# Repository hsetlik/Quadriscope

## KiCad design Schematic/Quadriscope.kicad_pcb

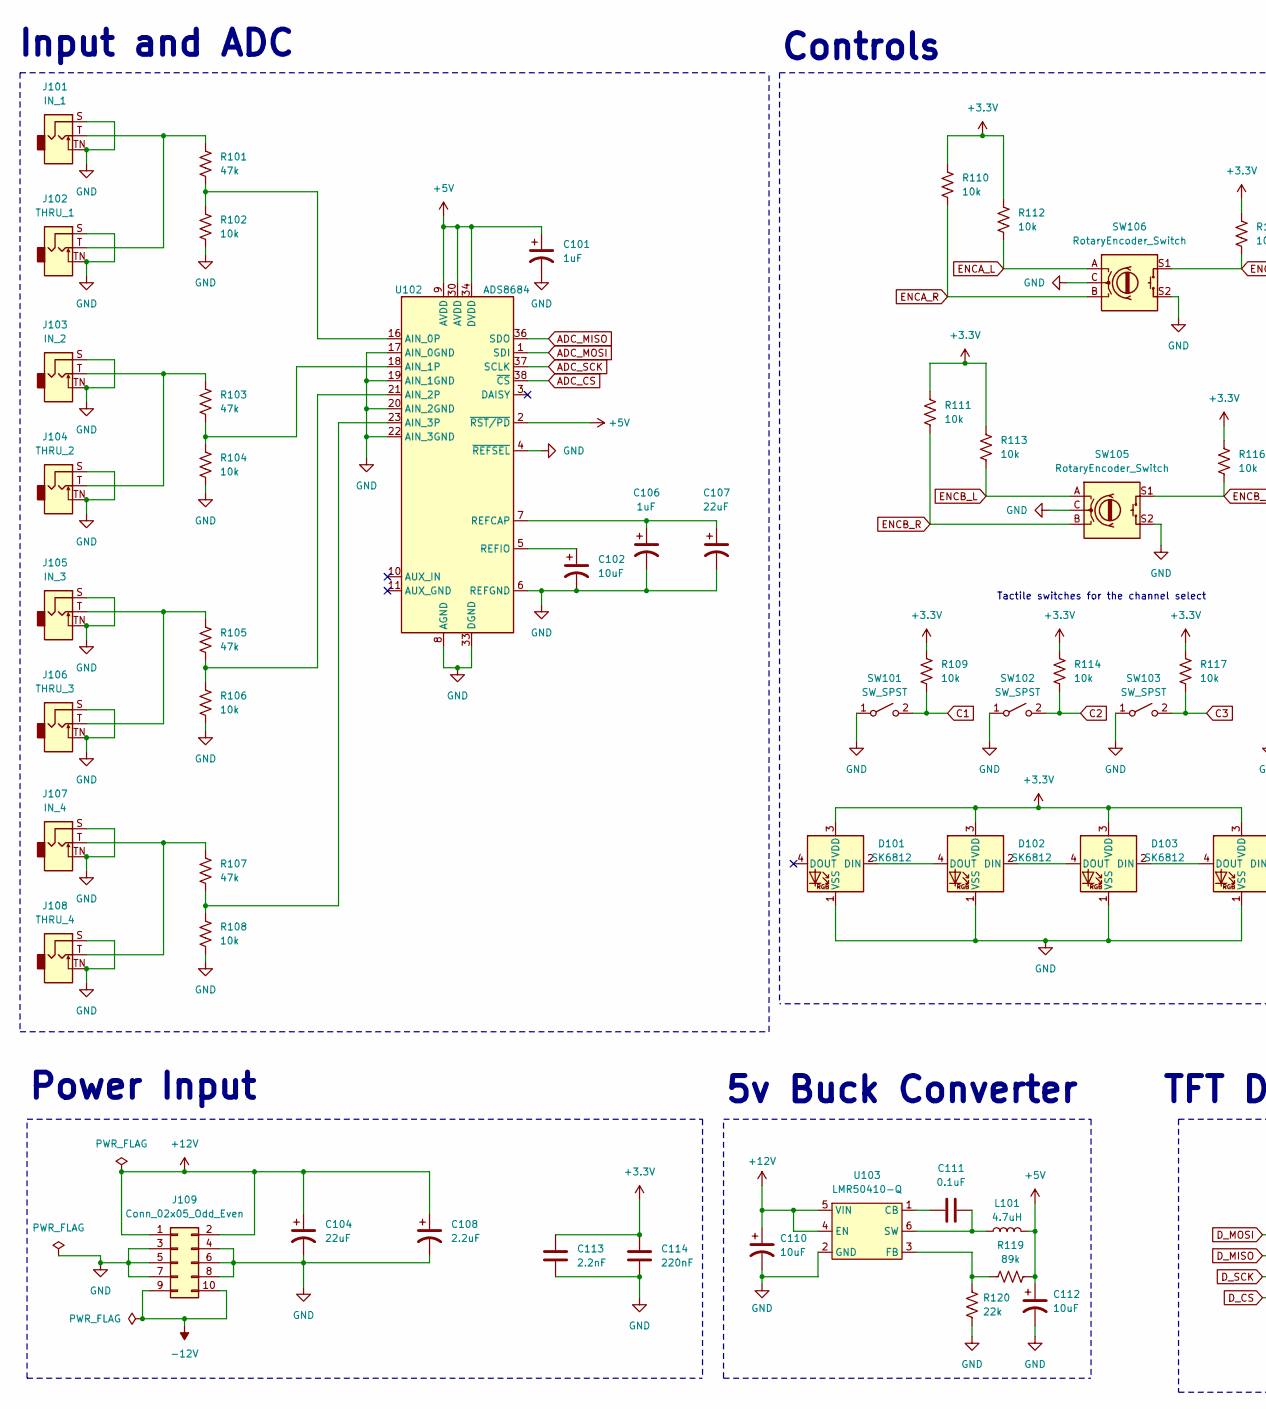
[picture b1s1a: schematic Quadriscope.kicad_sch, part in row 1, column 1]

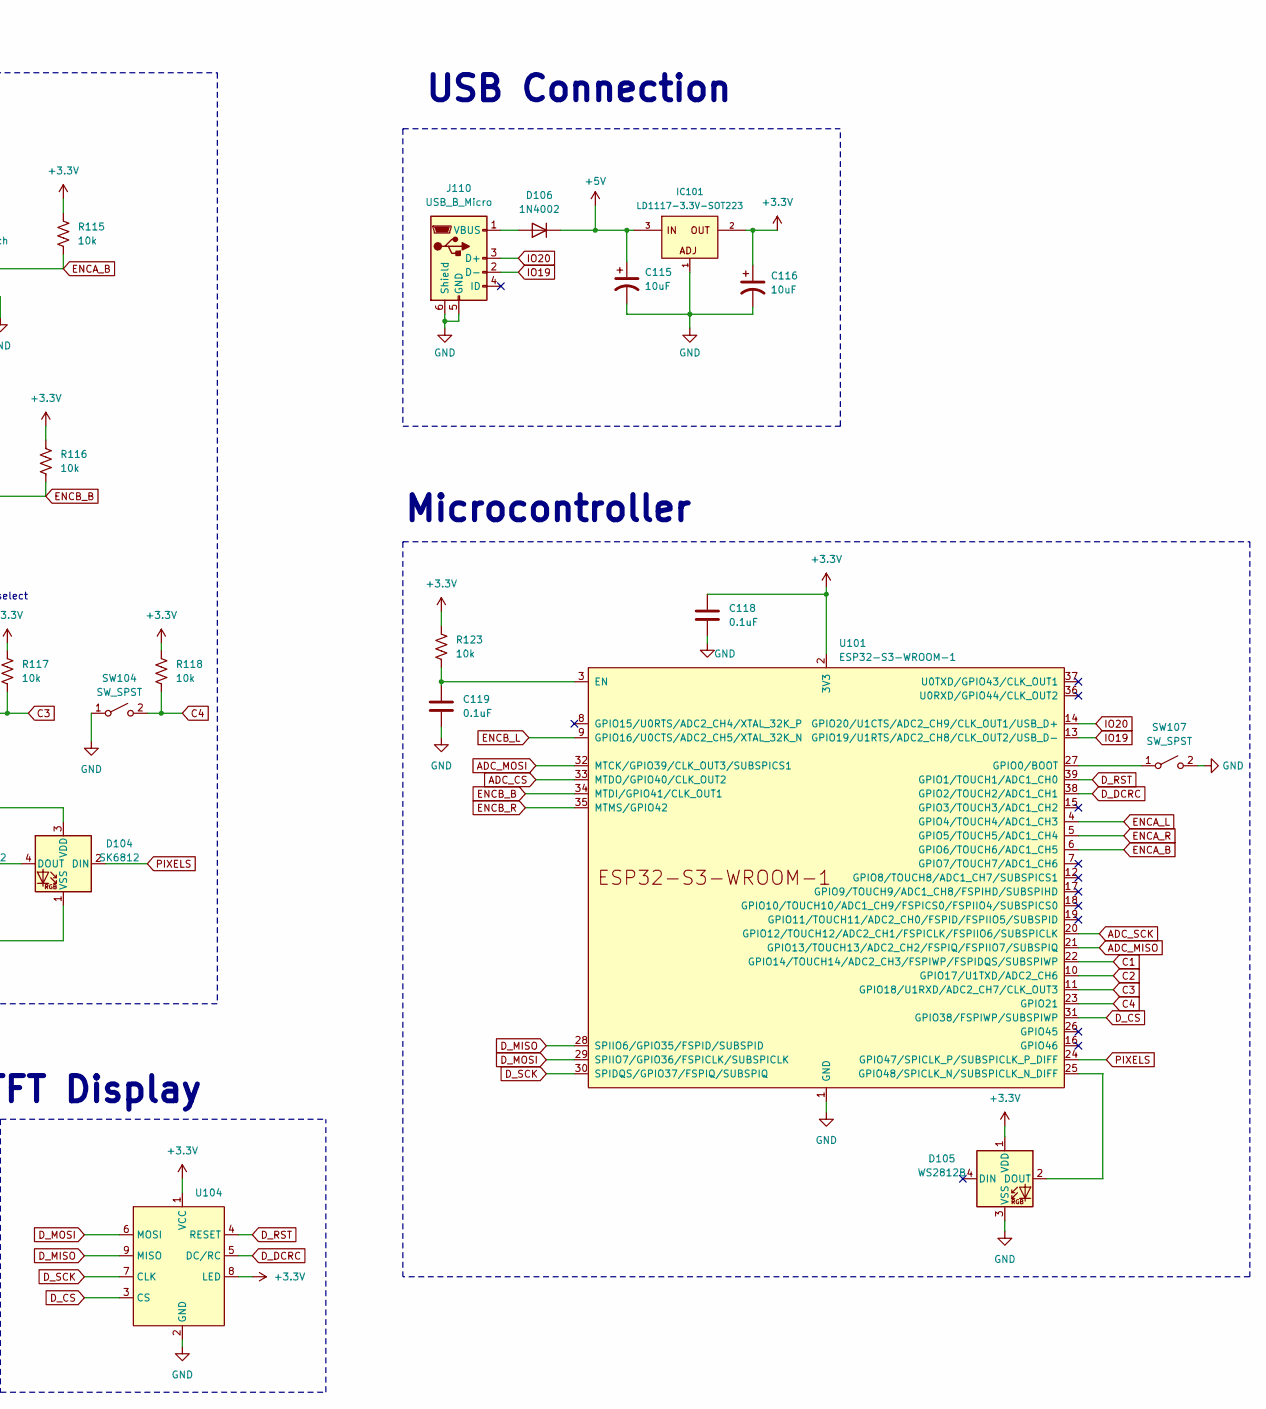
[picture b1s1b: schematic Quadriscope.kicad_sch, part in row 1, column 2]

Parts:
C101, C106: 1uF; CP_Radial_D5.0mm_P2.50mm
C102, C110, C112, C115, C116: 10uF; CP_Radial_D5.0mm_P2.50mm
C104, C107: 22uF; CP_Radial_D5.0mm_P2.50mm
C108: 2.2uF; CP_Radial_D5.0mm_P2.50mm
C111, C118, C119: 0.1uF; C_Disc_D4.7mm_W2.5mm_P5.00mm
C113: 2.2nF; C_Disc_D4.7mm_W2.5mm_P5.00mm
C114: 220nF; C_Disc_D4.7mm_W2.5mm_P5.00mm
D101, D102, D103, D104: SK6812; LED_SK6812_PLCC4_5.0x5.0mm_P3.2mm
D105: WS2812B; LED_SK6812_PLCC4_5.0x5.0mm_P3.2mm
D106: 1N4002; D_DO-41_SOD81_P10.16mm_Horizontal
IC101: LD1117-3.3V-SOT223; SOT-23; Part Number LD1117S33CTR
J101: IN_1; Jack_3.5mm_QingPu_WQP-PJ398SM_Vertical_CircularHoles
J102: THRU_1; Jack_3.5mm_QingPu_WQP-PJ398SM_Vertical_CircularHoles
J103: IN_2; Jack_3.5mm_QingPu_WQP-PJ398SM_Vertical_CircularHoles
J104: THRU_2; Jack_3.5mm_QingPu_WQP-PJ398SM_Vertical_CircularHoles
J105: IN_3; Jack_3.5mm_QingPu_WQP-PJ398SM_Vertical_CircularHoles
J106: THRU_3; Jack_3.5mm_QingPu_WQP-PJ398SM_Vertical_CircularHoles
J107: IN_4; Jack_3.5mm_QingPu_WQP-PJ398SM_Vertical_CircularHoles
J108: THRU_4; Jack_3.5mm_QingPu_WQP-PJ398SM_Vertical_CircularHoles
J109: Conn_02x05_Odd_Even; PinHeader_2x05_P2.54mm_Vertical
J110: USB_B_Micro; USB_Micro-B_Amphenol_10118193-0001LF_Horizontal
L101: 4.7uH; L_Bourns_SRP5030T
R101, R103, R105, R107: 47k; R_Axial_DIN0207_L6.3mm_D2.5mm_P7.62mm_Horizontal
R102, R104, R106, R108, R109, R110, R111, R112, R113, R114, R115, R116, R117, R118, R123: 10k; R_Axial_DIN0207_L6.3mm_D2.5mm_P7.62mm_Horizontal
R119: 89k; R_Axial_DIN0207_L6.3mm_D2.5mm_P7.62mm_Horizontal
R120: 22k; R_Axial_DIN0207_L6.3mm_D2.5mm_P7.62mm_Horizontal
SW101, SW102, SW103, SW104, SW107: SW_SPST; SW_PUSH_6mm_H5mm
SW105, SW106: RotaryEncoder_Switch; RotaryEncoder_Alps_EC11E-Switch_Vertical_H20mm_5Pin
U101: ESP32-S3-WROOM-1
U102: ADS8684; TSSOP-38_4.4x9.7mm_P0.5mm
U103: LMR50410-Q; SOT-23-6_BigPads
U104: TFTBreakout_ILI9341_340x320

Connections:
+3.3V: C113.1, C114.1, C116.1, C118.1, D101.3 (VDD), D102.3 (VDD), D103.3 (VDD), D104.3 (VDD), D105.1 (VDD), IC101.2 (OUT), R109.1, R110.1, R111.1, R112.1, R113.1, R114.1, R115.1, R116.1, R117.1, R118.1, R123.1, U101.2 (3V3), U104.1 (VCC), U104.8 (LED)
+5V: C101.1, C112.1, C115.1, D106.1 (K), IC101.3 (IN), L101.2, R119.2, U102.2 (~RST/PD), U102.9 (AVDD), U102.30 (AVDD), U102.34 (DVDD)
+12V: C104.1, C108.1, C110.1, J109.1, J109.2, U103.4 (EN), U103.5 (VIN)
-12V: J109.9, J109.10
ADC_CS: U101.33 (MTDO/GPIO40/CLK_OUT2), U102.38 (~CS)
ADC_MISO: U101.21 (GPIO13/TOUCH13/ADC2_CH2/FSPIQ/FSPIIO7/S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), U102.36 (SDO)
ADC_MOSI: U101.32 (MTCK/GPIO39/CLK_OUT3/SUBSPICS1), U102.1 (SDI)
ADC_SCK: U101.20 (GPIO12/TOUCH12/ADC2_CH1/FSPICLK/FSPIIO6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), U102.37 (SCLK)
C1: R109.2, SW101.2 (B), U101.22 (GPIO14/TOUCH14/ADC2_CH3/FSPIWP/FSPIDQS/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)
C2: R114.2, SW102.2 (B), U101.10 (GPIO17/U1TXD/ADC2_CH6)
C3: R117.2, SW103.2 (B), U101.11 (GPIO18/U1RXD/ADC2_CH7/CLK_OUT3)
C4: R118.2, SW104.2 (B), U101.23 (GPIO21)
D_CS: U101.31 (GPIO38/FSPIWP/SUBSPIWP), U104.3 (CS)
D_DCRC: U101.38 (GPIO2/TOUCH2/ADC1_CH1), U104.5 (DC/RC)
D_MISO: U101.28 (SPIIO6/GPIO35/FSPID/SUBSPID), U104.9 (MISO)
D_MOSI: U101.29 (SPIIO7/GPIO36/FSPICLK/SUBSPICLK), U104.6 (MOSI)
D_RST: U101.39 (GPIO1/TOUCH1/ADC1_CH0), U104.4 (RESET)
D_SCK: U101.30 (SPIDQS/GPIO37/FSPIQ/SUBSPIQ), U104.7 (CLK)
ENCA_B: R115.2, SW106.S1, U101.6 (GPIO6/TOUCH6/ADC1_CH5)
ENCA_L: R112.2, SW106.A, U101.4 (GPIO4/TOUCH4/ADC1_CH3)
ENCA_R: R110.2, SW106.B, U101.5 (GPIO5/TOUCH5/ADC1_CH4)
ENCB_B: R116.2, SW105.S1, U101.34 (MTDI/GPIO41/CLK_OUT1)
ENCB_L: R113.2, SW105.A, U101.9 (GPIO16/U0CTS/ADC2_CH5/XTAL_32K_N)
ENCB_R: R111.2, SW105.B, U101.35 (MTMS/GPIO42)
GND: C101.2, C102.2, C104.2, C106.2, C107.2, C108.2, C110.2, C112.2, C113.2, C114.2, C115.2, C116.2, C118.2, C119.2, D101.1 (VSS), D102.1 (VSS), D103.1 (VSS), D104.1 (VSS), D105.3 (VSS), IC101.1 (ADJ), J101.S, J101.TN, J102.S, J102.TN, J103.S, J103.TN, J104.S, J104.TN, J105.S, J105.TN, J106.S, J106.TN, J107.S, J107.TN, J108.S, J108.TN, J109.3, J109.4, J109.5, J109.6, J109.7, J109.8, J110.5 (GND), J110.6 (Shield), R102.2, R104.2, R106.2, R108.2, R120.2, SW101.1 (A), SW102.1 (A), SW103.1 (A), SW104.1 (A), SW105.C, SW105.S2, SW106.C, SW106.S2, SW107.2 (B), U101.1 (GND), U101.40 (GND), U101.41 (GND), U102.4 (~REFSEL), U102.6 (REFGND), U102.8 (AGND), U102.17 (AIN_0GND), U102.19 (AIN_1GND), U102.20 (AIN_2GND), U102.22 (AIN_3GND), U102.28 (AGND), U102.29 (AGND), U102.31 (AGND), U102.32 (AGND), U102.33 (DGND), U103.2 (GND), U104.2 (GND)
IO19: J110.2 (D-), U101.13 (GPIO19/U1RTS/ADC2_CH8/CLK_OUT2/USB_D-)
IO20: J110.3 (D+), U101.14 (GPIO20/U1CTS/ADC2_CH9/CLK_OUT1/USB_D+)
unnamed: D101.2 (DIN), D102.4 (DOUT)
unnamed: D102.2 (DIN), D103.4 (DOUT)
unnamed: D103.2 (DIN), D104.4 (DOUT)
unnamed: D105.2 (DOUT), U101.25 (GPIO48/SPICLK_N/SUBSPICLK_N_DIFF)
unnamed: D106.2 (A), J110.1 (VBUS)
unnamed: J101.T, J102.T, R101.1
unnamed: J103.T, J104.T, R103.1
unnamed: J105.T, J106.T, R105.1
unnamed: J107.T, J108.T, R107.1
unnamed: SW107.1 (A), U101.27 (GPIO0/BOOT)
unnamed: C119.1, R123.2, U101.3 (EN)
unnamed: R101.2, R102.1, U102.16 (AIN_0P)
unnamed: R103.2, R104.1, U102.18 (AIN_1P)
unnamed: R105.2, R106.1, U102.21 (AIN_2P)
unnamed: R107.2, R108.1, U102.23 (AIN_3P)
unnamed: C106.1, C107.1, U102.7 (REFCAP)
unnamed: C102.1, U102.5 (REFIO)
unnamed: C111.1, U103.1 (CB)
unnamed: R119.1, R120.1, U103.3 (FB)
unnamed: C111.2, L101.1, U103.6 (SW)
PIXELS: D104.2 (DIN), U101.24 (GPIO47/SPICLK_P/SUBSPICLK_P_DIFF)

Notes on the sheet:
Power Input
Microcontroller
USB Connection
Tactile switches for the channel select
TFT Display
5v Buck Converter
Input and ADC
Controls

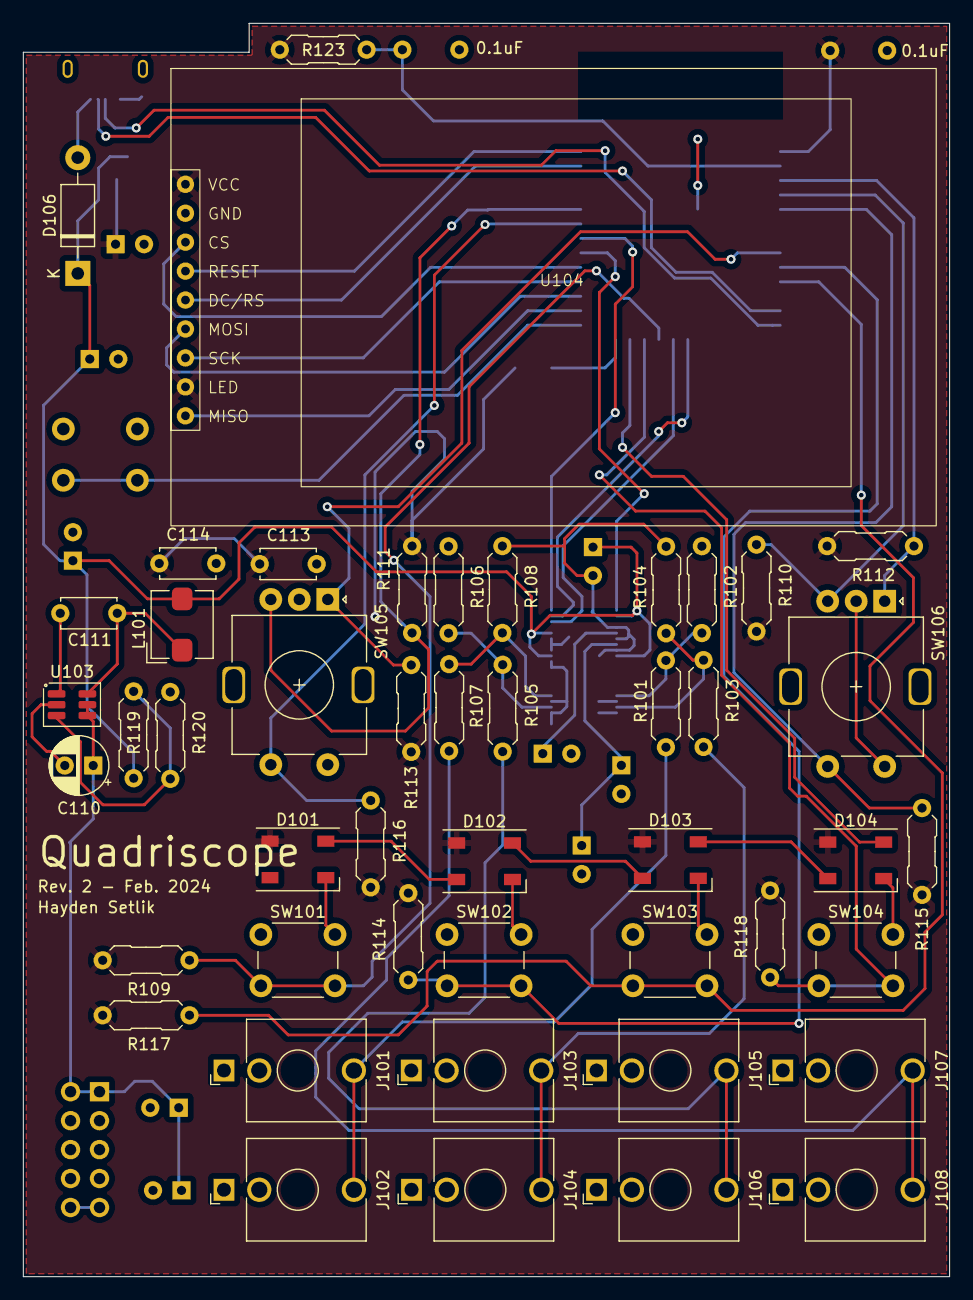
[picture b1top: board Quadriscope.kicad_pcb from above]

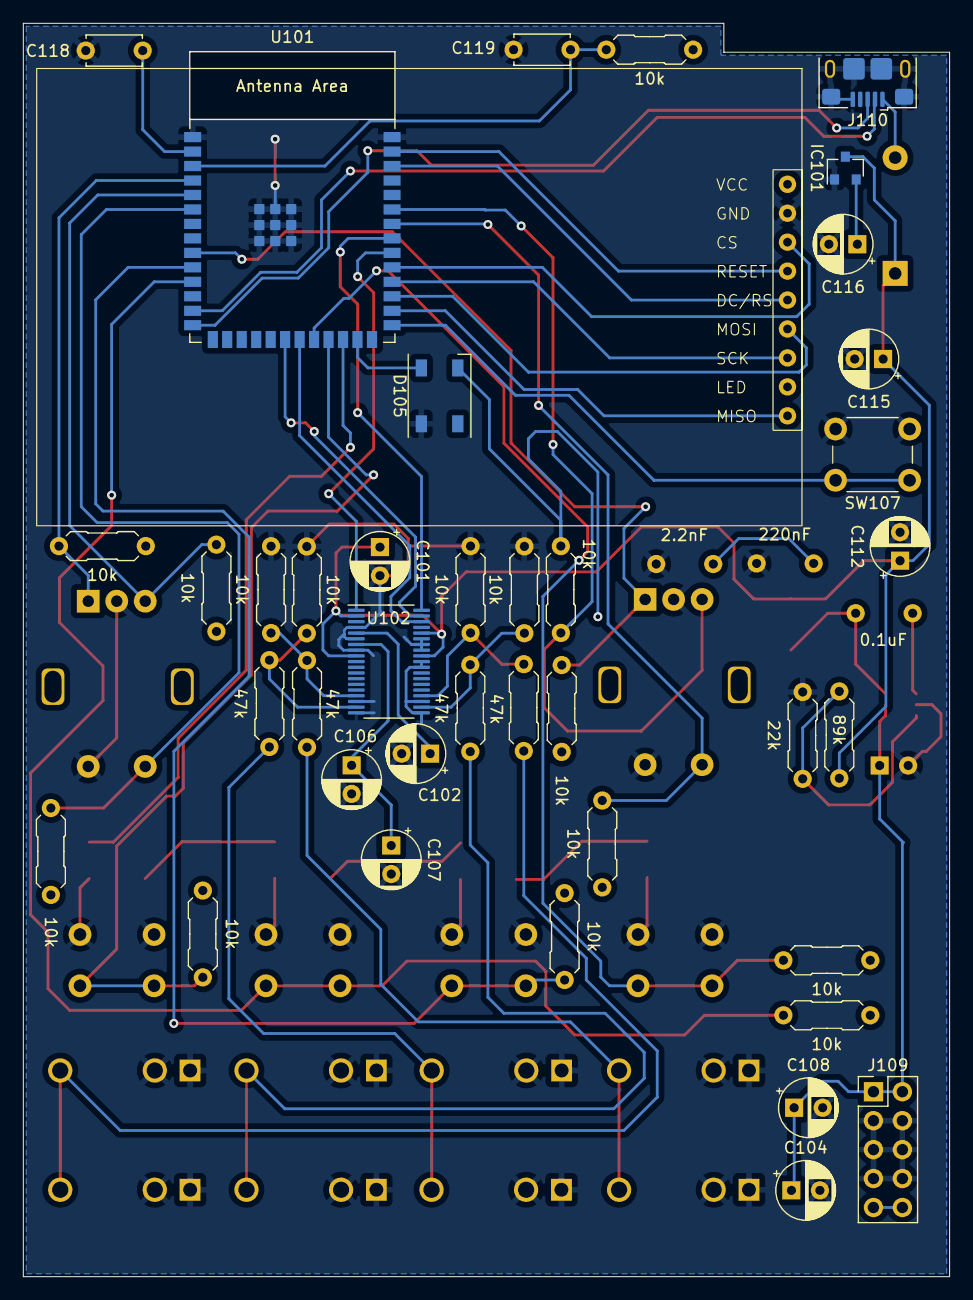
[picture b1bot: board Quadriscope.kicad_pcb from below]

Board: 2 copper layers, 81.3 x 110.0 mm, 65 parts (18 on the bottom side), 48 nets.

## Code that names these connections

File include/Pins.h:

#pragma once

// 4-wire SPI for the ADC
// these are the default pins for the S3's 
// built-in "FSPI" peripheral but I'll specify them to be safe
#define ADC_MOSI 39
#define ADC_MISO 13
#define ADC_SCK 12
#define ADC_CS 40

//another 4-wire SPI for the display, plus two extra pins
#define D_MOSI 36
#define D_MISO 35
#define D_SCK 37
#define D_CS 38
#define D_RST 1
#define D_DCRC 2

//two rotary encoders w/ buttons
#define ENCA_L 4
#define ENCA_R 5
#define ENCA_B 6
#define ENCB_L 16
#define ENCB_R 42
#define ENCB_B 41

// four channel select buttons
#define CH1 14
#define CH2 17
#define CH3 18
#define CH4 21

// NeoPixels
#define PIXELS 47

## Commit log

2024-02-17 dependencies, skeleton
2024-02-17 buttons, pixels
2024-02-24 new board file, interrupt stuff
2024-02-24 Big Buffers in PSRAM working
2024-02-25 display drawing logic
